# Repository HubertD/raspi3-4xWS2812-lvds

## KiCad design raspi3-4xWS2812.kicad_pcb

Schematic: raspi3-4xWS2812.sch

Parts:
C1, C2: 18pF; C_0603_1608Metric
C3, C4, C5: 1uF; C_0603_1608Metric
C6, C7, C8, C9, C10: 100nF; C_0603_1608Metric
D1: red; LED_0603_1608Metric
D2: yellow; LED_0603_1608Metric
J1: Conn_ARM_JTAG_SWD_10; PinHeader_2x05_P1.27mm_Vertical
J2: Raspberry_Pi_2_3; PinHeader_2x20_P2.54mm_Vertical
J4: Conn_02x04_Odd_Even; PinHeader_2x04_P2.54mm_Vertical
R1, R2: 10K; R_0603_1608Metric
R3, R4: 1K; R_0603_1608Metric
R5, R6, R7, R8: 47R; R_0603_1608Metric
U1: SAMC21G18A-A; TQFP-48_7x7mm_P0.5mm
U2: 74LS86; SOIC-14_3.9x8.7mm_P1.27mm
Y1: 8MHz; Crystal_SMD_Abracon_ABM3-2Pin_5.0x3.2mm

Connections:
+3V3: C5.1, C7.1, C8.1, C9.1, C10.1, J1.1, J2.1, J2.17, R1.1, R2.1, R3.1, R4.1, U1.6 (VDDA), U1.17 (VDDIO), U1.36 (VDDIO), U1.44 (VDDIN)
+5V: C3.1, J2.2, J2.4, U2.14
GND: C1.2, C2.2, C3.2, C4.2, C5.2, C6.2, C7.2, C8.2, C9.2, C10.2, J1.3, J1.5, J1.9, J2.6, J2.9, J2.14, J2.20, J2.25, J2.30, J2.34, J2.39, J4.2, J4.4, J4.6, J4.8, U1.5 (GNDA), U1.18 (GND), U1.35 (GND), U1.42 (GND), U2.7
GPIO_A01: J2.15, U1.15 (PA10)
GPIO_A02: J2.16, U1.14 (PA09)
GPIO_A03: J2.18, U1.13 (PA08)
INVERT: U1.16 (PA11), U2.2, U2.5, U2.10, U2.13
LED0: D1.1, U1.37 (PB22)
LED1: D2.1, U1.38 (PB23)
NRST: J1.10, J2.33, R2.2, U1.40 (NRST)
unnamed: C1.1, U1.23 (PA14), Y1.1
unnamed: C2.1, U1.24 (PA15), Y1.2
unnamed: C4.1, C6.1, U1.43 (VDDCORE)
unnamed: D1.2, R3.2
unnamed: D2.2, R4.2
unnamed: J4.1, R5.1
unnamed: J4.3, R6.1
unnamed: J4.5, R7.1
unnamed: J4.7, R8.1
unnamed: R5.2, U2.3
unnamed: R6.2, U2.6
unnamed: R7.2, U2.8
unnamed: R8.2, U2.11
SPI0_CS: J2.24, U1.11 (PA06)
SPI0_MISO: J2.21, U1.9 (PA04)
SPI0_MOSI: J2.19, U1.12 (PA07)
SPI0_SCK: J2.23, U1.10 (PA05)
SPI1_MOSI: U1.1 (PA00), U2.9
SPI2_MOSI: U1.21 (PA12), U2.4
SPI3_MOSI: U1.25 (PA16), U2.1
SPI4_MOSI: U1.7 (PB08), U2.12
SWCLK: J1.4, J2.32, R1.2, U1.45 (PA30)
SWDIO: J1.2, J2.31, U1.46 (PA31)
UART5_RX: J2.8, U1.30 (PA21)
UART5_TX: J2.10, U1.29 (PA20)

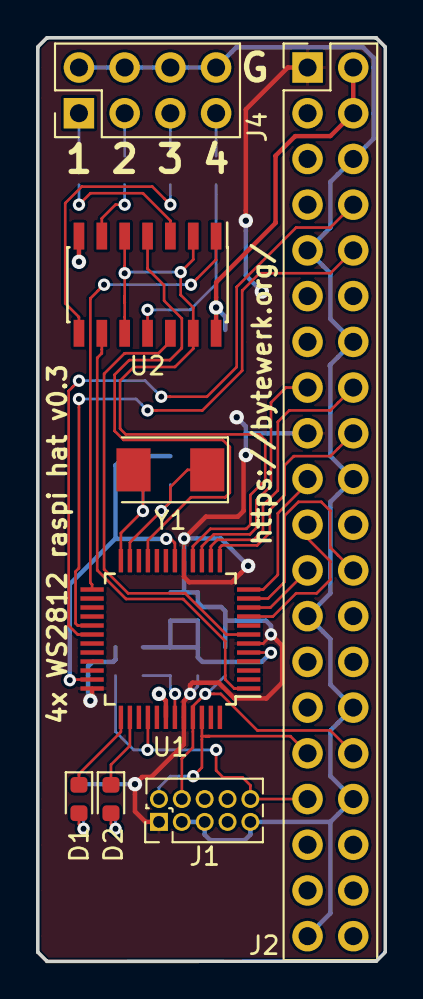
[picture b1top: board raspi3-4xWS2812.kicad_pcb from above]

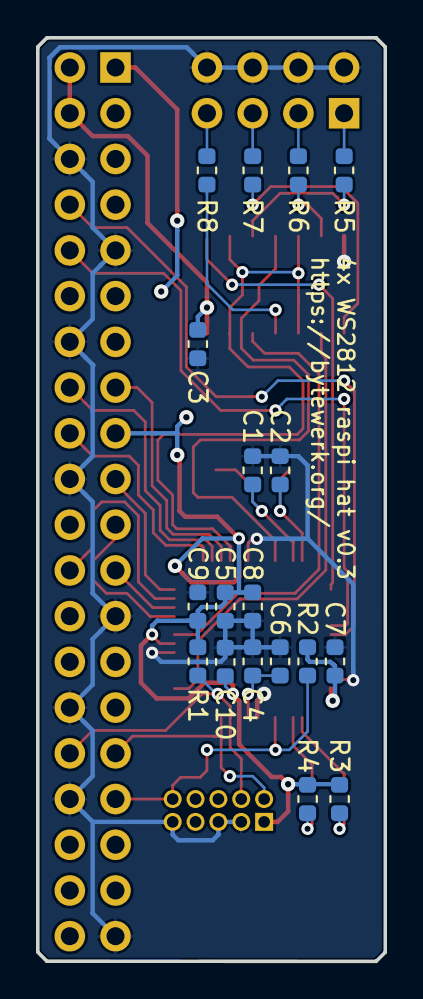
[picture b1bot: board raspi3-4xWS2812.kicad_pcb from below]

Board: 2 copper layers, 19.3 x 51.3 mm, 26 parts (18 on the bottom side), 35 nets.

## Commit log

2018-06-25 initial checkin
2018-06-25 add schematics.pdf
2018-06-25 add quad OR gate as level shifter
2018-06-25 annotate U4
2018-06-26 board layout!
2018-06-27 improve silkscreen, make jtag connector through hole
2018-06-28 add gerbers
2018-06-28 remove old project file
2018-07-31 v0.3
2018-08-31 fix fabrication layer
